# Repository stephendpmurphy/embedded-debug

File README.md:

# embedded-debug

This debug board allows two unused traces of a 10pin (1.27mm pitch) connector to be broken out and used for a UART RX & TX line from the target MCU. These UART lines can be used by the Target to send debug print statements through the programming connector, to the USB bridge, and then displayed on a PC terminal. This is useful since board space is no longer needed on the target for any sort of extra headers or test pads for debug data.

This is a revamp of an existing project [ARM-Debug](https://github.com/stephendpmurphy/ARM-Debug) which was originally designed in Eagle CAD, while this project is designed using [KiCAD](https://kicad-pcb.org/)

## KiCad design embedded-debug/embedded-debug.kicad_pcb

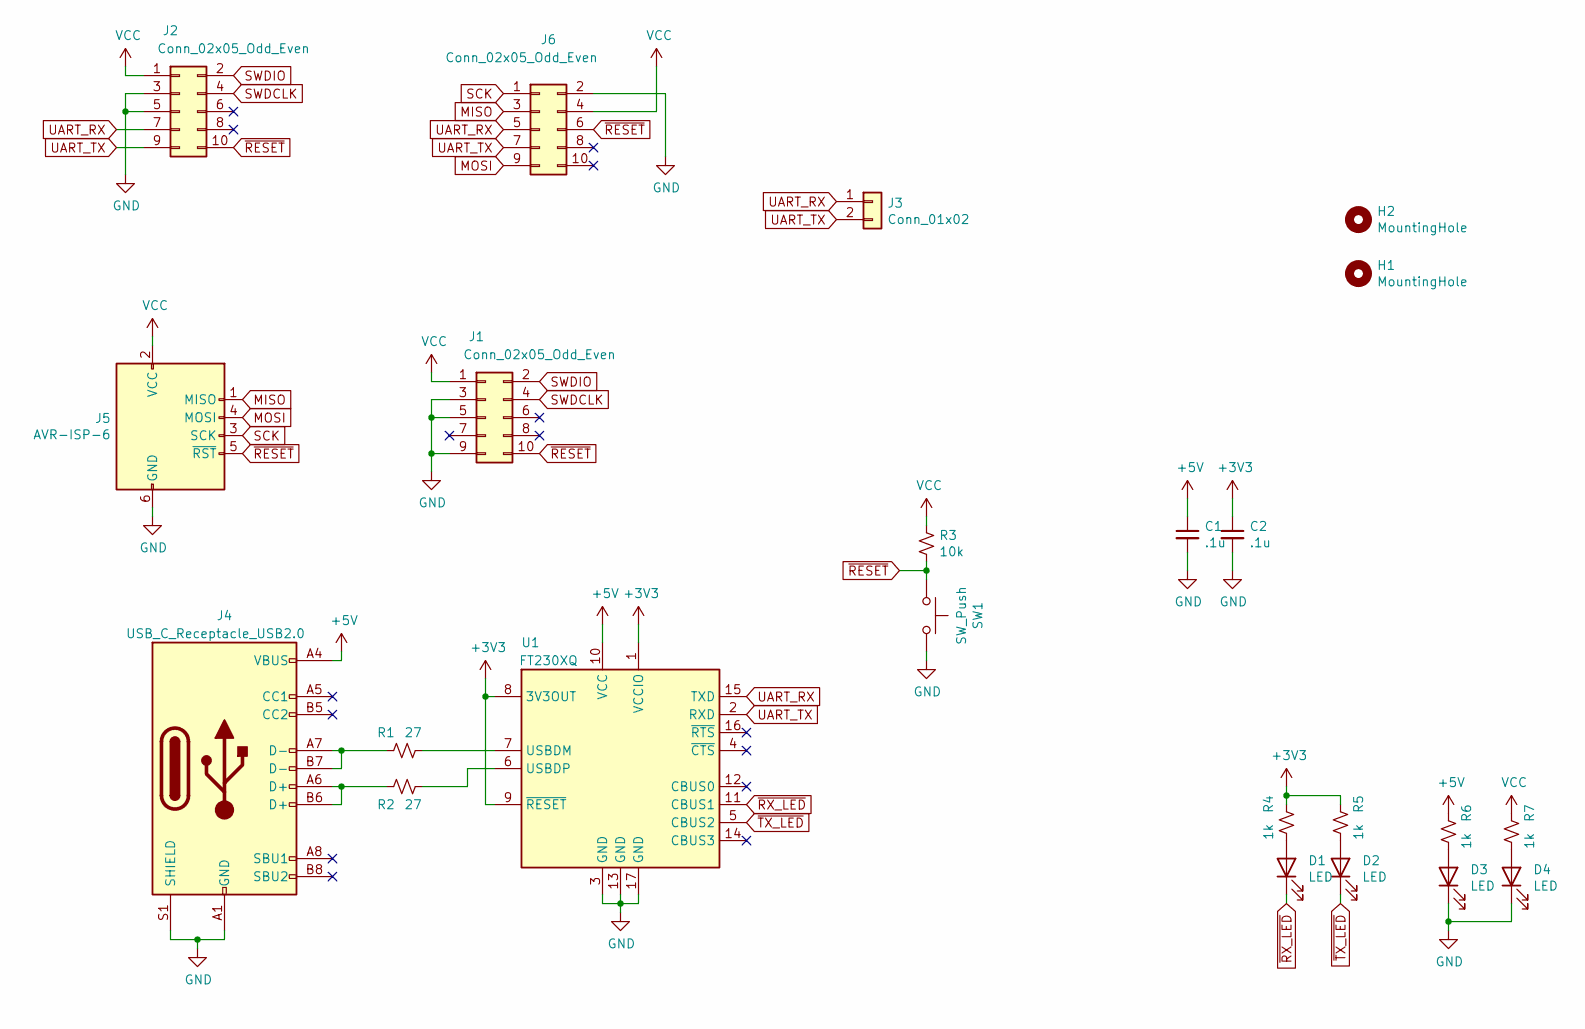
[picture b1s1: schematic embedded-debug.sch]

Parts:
C1, C2: .1u; C_0402_1005Metric
D1, D2, D3, D4: LED; LED_0603_1608Metric
H1, H2: MountingHole; MountingHole_2mm
J1, J2, J6: Conn_02x05_Odd_Even; PinHeader_2x05_P1.27mm_Vertical_SMD
J3: Conn_01x02; PinHeader_1x02_P2.54mm_Horizontal
J4: USB_C_Receptacle_USB2.0; USB_C_Receptacle_GCT_USB4085
J5: AVR-ISP-6; PinHeader_2x03_P2.54mm_Vertical
R1, R2: 27; R_0402_1005Metric
R3: 10k; R_0402_1005Metric
R4, R5, R6, R7: 1k; R_0402_1005Metric
SW1: SW_Push; Panasonic_EVQPUJ_EVQPUA
U1: FT230XQ; QFN-16-1EP_4x4mm_P0.65mm_EP2.1x2.1mm

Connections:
+3V3: C2.1, R4.1, R5.1, U1.1 (VCCIO), U1.8 (3V3OUT), U1.9 (~RESET)
+5V: C1.1, J4.A4 (VBUS), J4.A9 (VBUS), J4.B4 (VBUS), J4.B9 (VBUS), R6.1, U1.10 (VCC)
GND: C1.2, C2.2, D3.1 (K), D4.1 (K), J1.3, J1.5, J1.9, J2.3, J2.5, J4.A1 (GND), J4.A12 (GND), J4.B1 (GND), J4.B12 (GND), J4.S1 (SHIELD), J5.6 (GND), J6.2, SW1.2, U1.3 (GND), U1.13 (GND), U1.17 (GND)
MISO: J5.1 (MISO), J6.3
MOSI: J5.4 (MOSI), J6.9
unnamed: D1.2 (A), R4.2
unnamed: D2.2 (A), R5.2
unnamed: D3.2 (A), R6.2
unnamed: D4.2 (A), R7.2
unnamed: J4.A6 (D+), J4.B6 (D+), R2.1
unnamed: J4.A7 (D-), J4.B7 (D-), R1.1
unnamed: R1.2, U1.7 (USBDM)
unnamed: R2.2, U1.6 (USBDP)
SCK: J5.3 (SCK), J6.1
SWDCLK: J1.4, J2.4
SWDIO: J1.2, J2.2
UART_RX: J2.7, J3.1, J6.5, U1.15 (TXD)
UART_TX: J2.9, J3.2, J6.7, U1.2 (RXD)
VCC: J1.1, J2.1, J5.2 (VCC), J6.4, R3.1, R7.1
~RESET: J1.10, J2.10, J5.5 (~RST), J6.6, R3.2, SW1.1
~RX_LED: D1.1 (K), U1.11 (CBUS1)
~TX_LED: D2.1 (K), U1.5 (CBUS2)

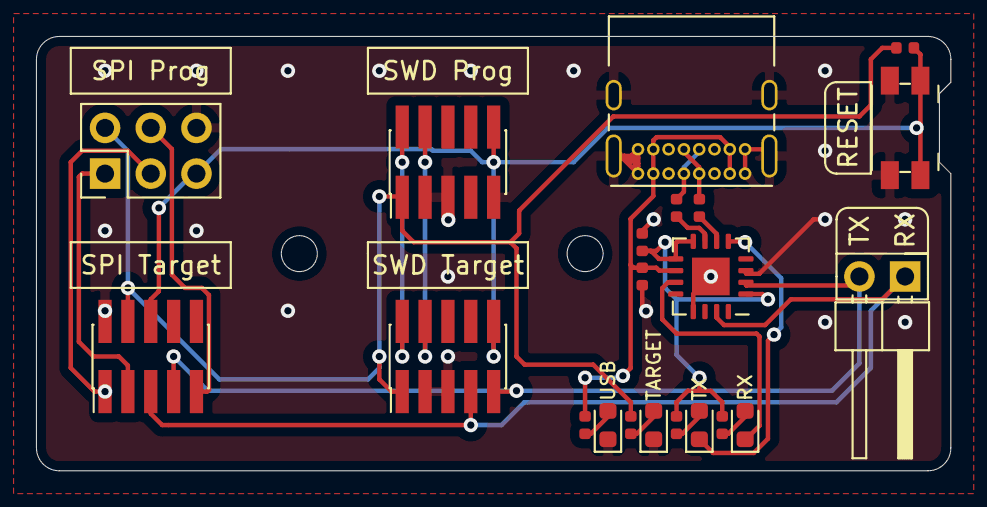
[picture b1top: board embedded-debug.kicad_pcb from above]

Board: 2 copper layers, 50.8 x 24.1 mm, 23 parts (0 on the bottom side), 22 nets.

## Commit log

2020-09-26 First pass at routing
2020-10-02 Committing and order rev-1
2020-10-05 Updating License badge

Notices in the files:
README.md:
License: CC-BY-SA
embedded-debug/embedded-debug.kicad_pcb:
CC-BY-SA
